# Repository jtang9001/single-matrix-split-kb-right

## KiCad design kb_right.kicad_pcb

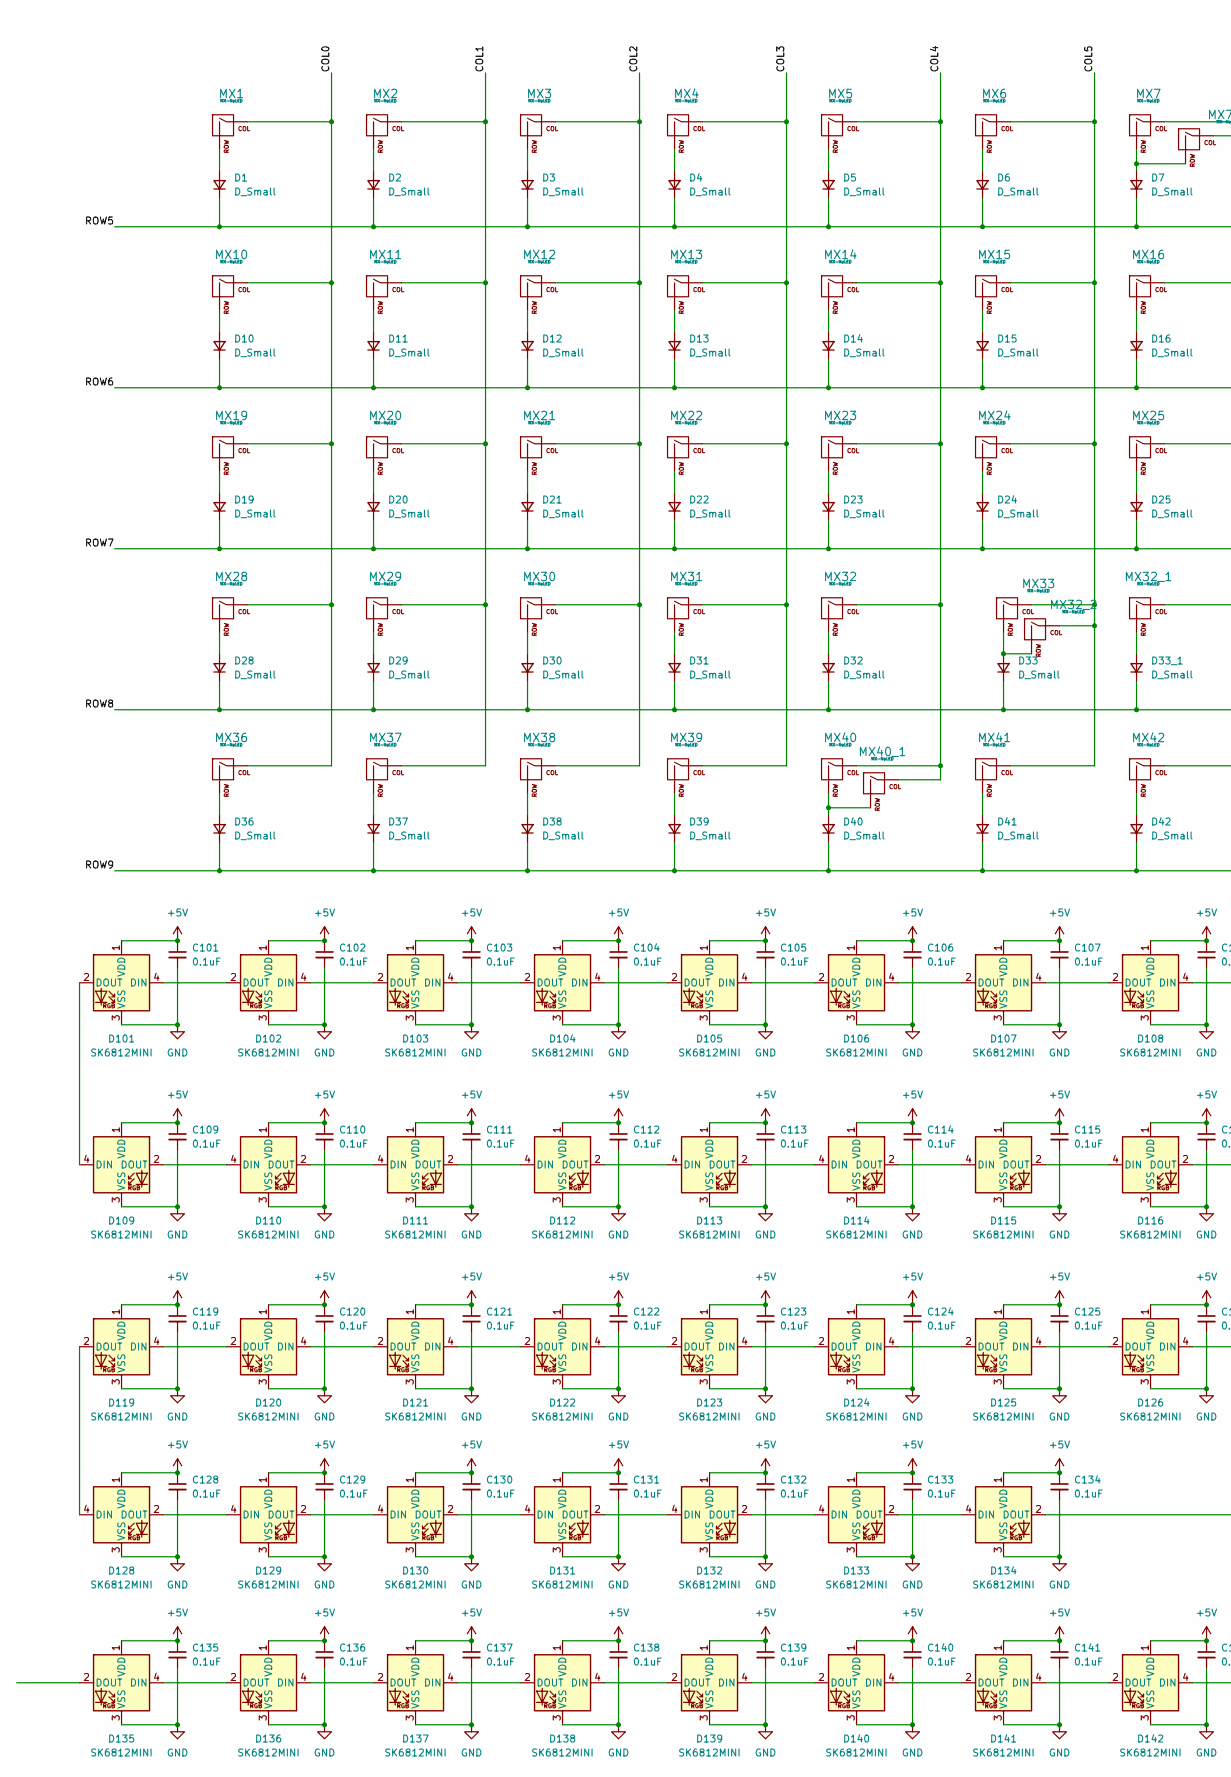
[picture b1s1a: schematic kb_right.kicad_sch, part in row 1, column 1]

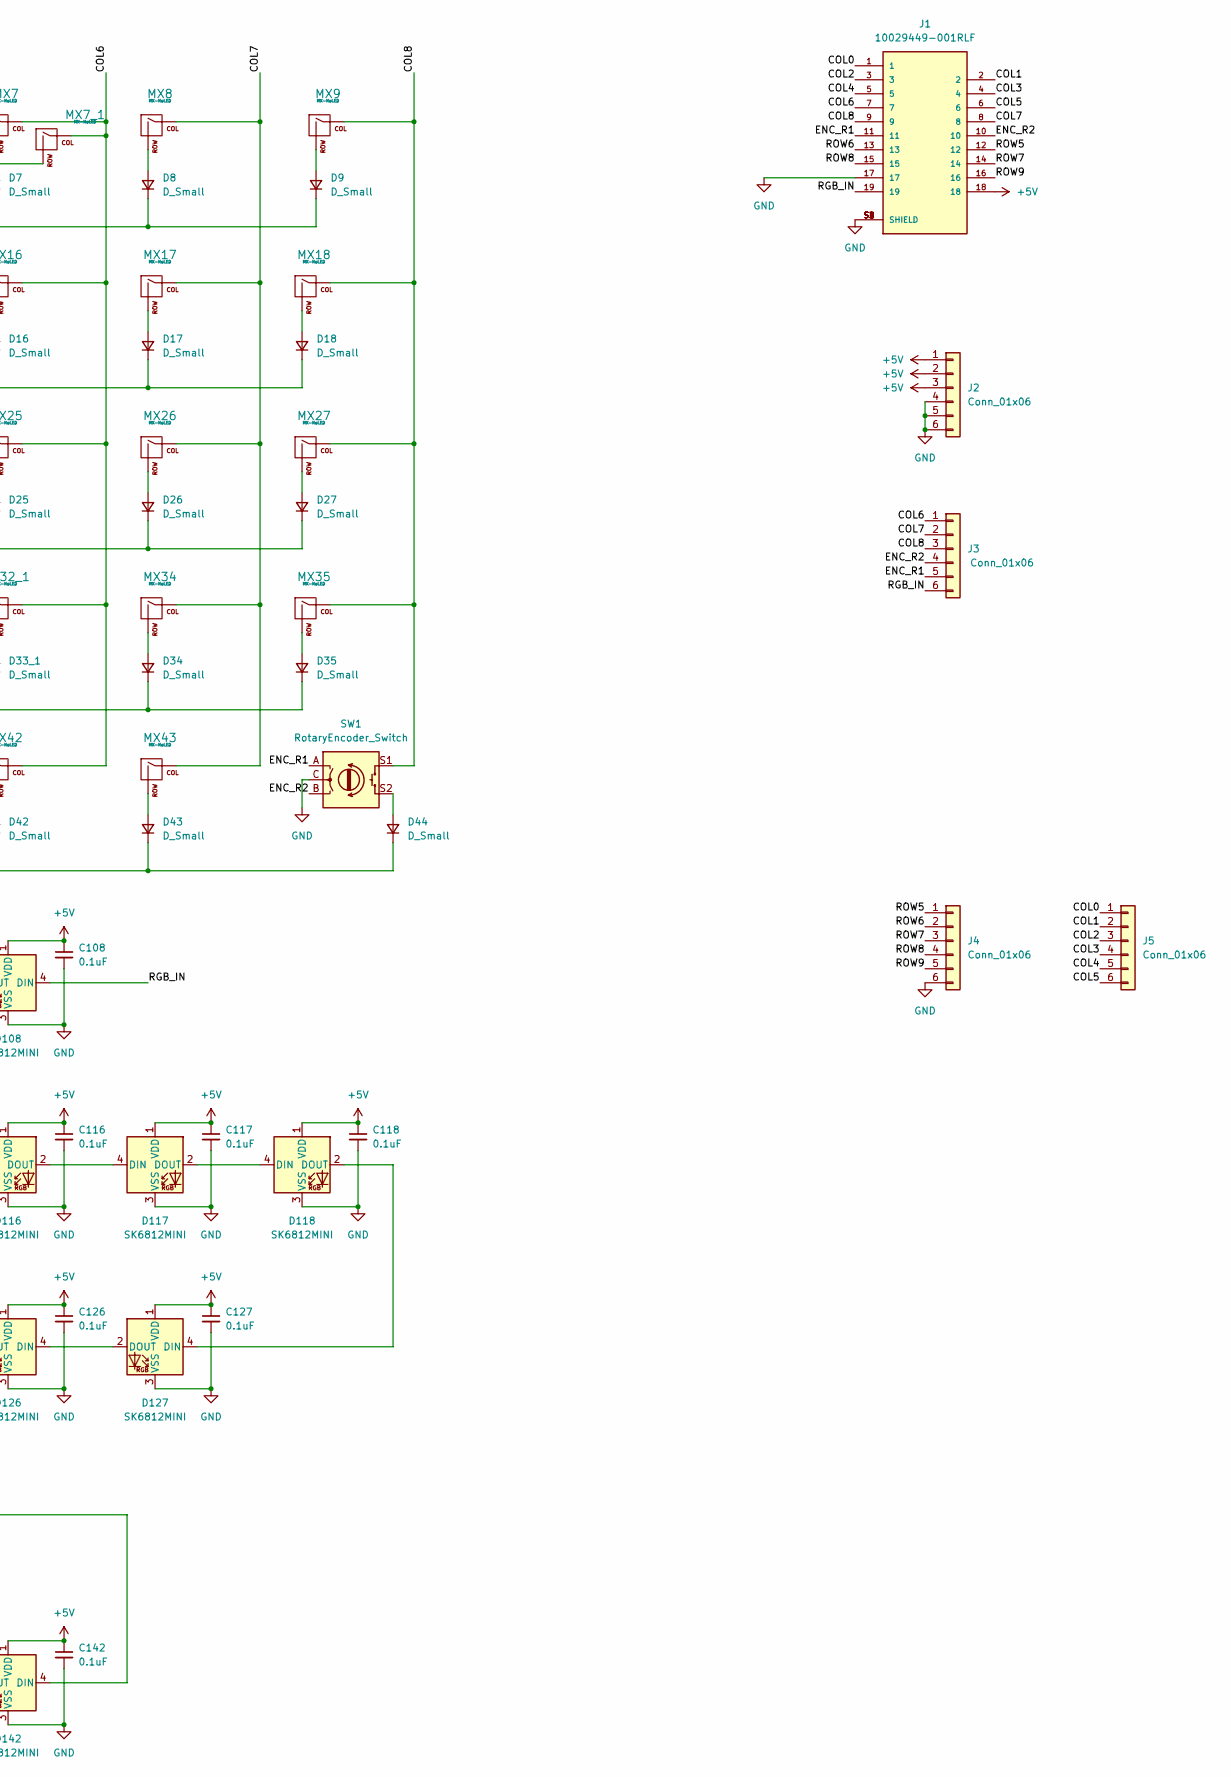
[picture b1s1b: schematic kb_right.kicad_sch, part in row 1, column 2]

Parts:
C101, C102, C103, C104, C105, C106, C107, C108, C109, C110, C111, C112, C113, C114, C115, C116, C117, C118, C119, C120, C121, C122, C123, C124, C125, C126, C127, C128, C129, C130, C131, C132, C133, C134, C135, C136, C137, C138, C139, C140, C141, C142: 0.1uF; C_0805_2012Metric_Pad1.18x1.45mm_HandSolder
D1, D2, D3, D4, D5, D6, D10, D11, D12, D13, D14, D15, D19, D20, D21, D22, D23, D24, D28, D29, D30, D31, D32, D33, D36, D37, D38, D39, D40, D41: D_Small; Diode-Hybrid-Back
D7, D8, D9, D16, D17, D18, D25, D26, D27, D33_1, D34, D35, D42, D43, D44: D_Small; D_SOD-123
D101, D102, D103, D104, D105, D106, D107, D108, D109, D110, D111, D112, D113, D114, D115, D116, D117, D118, D119, D120, D121, D122, D123, D124, D125, D126, D127, D128, D129, D130, D131, D132, D133, D134, D135, D136, D137, D138, D139, D140, D141, D142: SK6812MINI; SK6812-MINI-E
J1: 10029449-001RLF; AMPHENOL_10029449-001RLF; PARTREV V
J2, J3, J4, J5: Conn_01x06; PinHeader_1x06_P2.54mm_Vertical
MX1, MX2, MX3, MX4, MX5, MX6, MX7, MX8, MX9, MX10, MX11, MX12, MX13, MX14, MX15, MX16, MX18, MX19, MX20, MX21, MX22, MX23, MX24, MX26, MX27, MX28, MX29, MX30, MX31, MX32, MX32_1, MX34, MX35, MX41, MX42, MX43: MX-NoLED; MXOnly-1U-Hotswap
MX7_1: MX-NoLED; MXOnly-2U-Hotswap
MX17, MX36, MX40_1: MX-NoLED; MXOnly-1.5U-Hotswap
MX25: MX-NoLED; MXOnly-2.25U-Hotswap
MX32_2: MX-NoLED; MXOnly-1.75U-Hotswap
MX33: MX-NoLED; MXOnly-2.75U-Hotswap
MX37, MX38, MX39, MX40: MX-NoLED; MXOnly-1.25U-Hotswap
SW1: RotaryEncoder_Switch; RotaryEncoder_EC11

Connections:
+5V: C101.1, C102.1, C103.1, C104.1, C105.1, C106.1, C107.1, C108.1, C109.1, C110.1, C111.1, C112.1, C113.1, C114.1, C115.1, C116.1, C117.1, C118.1, C119.1, C120.1, C121.1, C122.1, C123.1, C124.1, C125.1, C126.1, C127.1, C128.1, C129.1, C130.1, C131.1, C132.1, C133.1, C134.1, C135.1, C136.1, C137.1, C138.1, C139.1, C140.1, C141.1, C142.1, D101.1 (VDD), D102.1 (VDD), D103.1 (VDD), D104.1 (VDD), D105.1 (VDD), D106.1 (VDD), D107.1 (VDD), D108.1 (VDD), D109.1 (VDD), D110.1 (VDD), D111.1 (VDD), D112.1 (VDD), D113.1 (VDD), D114.1 (VDD), D115.1 (VDD), D116.1 (VDD), D117.1 (VDD), D118.1 (VDD), D119.1 (VDD), D120.1 (VDD), D121.1 (VDD), D122.1 (VDD), D123.1 (VDD), D124.1 (VDD), D125.1 (VDD), D126.1 (VDD), D127.1 (VDD), D128.1 (VDD), D129.1 (VDD), D130.1 (VDD), D131.1 (VDD), D132.1 (VDD), D133.1 (VDD), D134.1 (VDD), D135.1 (VDD), D136.1 (VDD), D137.1 (VDD), D138.1 (VDD), D139.1 (VDD), D140.1 (VDD), D141.1 (VDD), D142.1 (VDD), J1.18, J2.1, J2.2, J2.3
/COL0: J1.1, J5.1, MX1.1 (COL), MX10.1 (COL), MX19.1 (COL), MX28.1 (COL), MX36.1 (COL)
/COL1: J1.2, J5.2, MX2.1 (COL), MX11.1 (COL), MX20.1 (COL), MX29.1 (COL), MX37.1 (COL)
/COL2: J1.3, J5.3, MX3.1 (COL), MX12.1 (COL), MX21.1 (COL), MX30.1 (COL), MX38.1 (COL)
/COL3: J1.4, J5.4, MX4.1 (COL), MX13.1 (COL), MX22.1 (COL), MX31.1 (COL), MX39.1 (COL)
/COL4: J1.5, J5.5, MX5.1 (COL), MX14.1 (COL), MX23.1 (COL), MX32.1 (COL), MX40.1 (COL), MX40_1.1 (COL)
/COL5: J1.6, J5.6, MX6.1 (COL), MX15.1 (COL), MX24.1 (COL), MX32_2.1 (COL), MX33.1 (COL), MX41.1 (COL)
/COL6: J1.7, J3.1, MX7.1 (COL), MX7_1.1 (COL), MX16.1 (COL), MX25.1 (COL), MX32_1.1 (COL), MX42.1 (COL)
/COL7: J1.8, J3.2, MX8.1 (COL), MX17.1 (COL), MX26.1 (COL), MX34.1 (COL), MX43.1 (COL)
/COL8: J1.9, J3.3, MX9.1 (COL), MX18.1 (COL), MX27.1 (COL), MX35.1 (COL), SW1.S1
/ENC_R1: J1.11, J3.5, SW1.A
/ENC_R2: J1.10, J3.4, SW1.B
/RGB_IN: D108.4 (DIN), J1.19, J3.6
/ROW5: D1.1 (K), D2.1 (K), D3.1 (K), D4.1 (K), D5.1 (K), D6.1 (K), D7.1 (K), D8.1 (K), D9.1 (K), J1.12, J4.1
/ROW6: D10.1 (K), D11.1 (K), D12.1 (K), D13.1 (K), D14.1 (K), D15.1 (K), D16.1 (K), D17.1 (K), D18.1 (K), J1.13, J4.2
/ROW7: D19.1 (K), D20.1 (K), D21.1 (K), D22.1 (K), D23.1 (K), D24.1 (K), D25.1 (K), D26.1 (K), D27.1 (K), J1.14, J4.3
/ROW8: D28.1 (K), D29.1 (K), D30.1 (K), D31.1 (K), D32.1 (K), D33.1 (K), D33_1.1 (K), D34.1 (K), D35.1 (K), J1.15, J4.4
/ROW9: D36.1 (K), D37.1 (K), D38.1 (K), D39.1 (K), D40.1 (K), D41.1 (K), D42.1 (K), D43.1 (K), D44.1 (K), J1.16, J4.5
GND: C101.2, C102.2, C103.2, C104.2, C105.2, C106.2, C107.2, C108.2, C109.2, C110.2, C111.2, C112.2, C113.2, C114.2, C115.2, C116.2, C117.2, C118.2, C119.2, C120.2, C121.2, C122.2, C123.2, C124.2, C125.2, C126.2, C127.2, C128.2, C129.2, C130.2, C131.2, C132.2, C133.2, C134.2, C135.2, C136.2, C137.2, C138.2, C139.2, C140.2, C141.2, C142.2, D101.3 (VSS), D102.3 (VSS), D103.3 (VSS), D104.3 (VSS), D105.3 (VSS), D106.3 (VSS), D107.3 (VSS), D108.3 (VSS), D109.3 (VSS), D110.3 (VSS), D111.3 (VSS), D112.3 (VSS), D113.3 (VSS), D114.3 (VSS), D115.3 (VSS), D116.3 (VSS), D117.3 (VSS), D118.3 (VSS), D119.3 (VSS), D120.3 (VSS), D121.3 (VSS), D122.3 (VSS), D123.3 (VSS), D124.3 (VSS), D125.3 (VSS), D126.3 (VSS), D127.3 (VSS), D128.3 (VSS), D129.3 (VSS), D130.3 (VSS), D131.3 (VSS), D132.3 (VSS), D133.3 (VSS), D134.3 (VSS), D135.3 (VSS), D136.3 (VSS), D137.3 (VSS), D138.3 (VSS), D139.3 (VSS), D140.3 (VSS), D141.3 (VSS), D142.3 (VSS), J1.17, J1.S1 (SHIELD), J1.S2 (SHIELD), J1.S3 (SHIELD), J1.S4 (SHIELD), J2.4, J2.5, J2.6, J4.6, SW1.C
unnamed: D1.2 (A), MX1.2 (ROW)
unnamed: D2.2 (A), MX2.2 (ROW)
unnamed: D3.2 (A), MX3.2 (ROW)
unnamed: D4.2 (A), MX4.2 (ROW)
unnamed: D5.2 (A), MX5.2 (ROW)
unnamed: D6.2 (A), MX6.2 (ROW)
unnamed: D7.2 (A), MX7.2 (ROW), MX7_1.2 (ROW)
unnamed: D8.2 (A), MX8.2 (ROW)
unnamed: D9.2 (A), MX9.2 (ROW)
unnamed: D10.2 (A), MX10.2 (ROW)
unnamed: D11.2 (A), MX11.2 (ROW)
unnamed: D12.2 (A), MX12.2 (ROW)
unnamed: D13.2 (A), MX13.2 (ROW)
unnamed: D14.2 (A), MX14.2 (ROW)
unnamed: D15.2 (A), MX15.2 (ROW)
unnamed: D16.2 (A), MX16.2 (ROW)
unnamed: D17.2 (A), MX17.2 (ROW)
unnamed: D18.2 (A), MX18.2 (ROW)
unnamed: D19.2 (A), MX19.2 (ROW)
unnamed: D20.2 (A), MX20.2 (ROW)
unnamed: D21.2 (A), MX21.2 (ROW)
unnamed: D22.2 (A), MX22.2 (ROW)
unnamed: D23.2 (A), MX23.2 (ROW)
unnamed: D24.2 (A), MX24.2 (ROW)
unnamed: D25.2 (A), MX25.2 (ROW)
unnamed: D26.2 (A), MX26.2 (ROW)
unnamed: D27.2 (A), MX27.2 (ROW)
unnamed: D28.2 (A), MX28.2 (ROW)
unnamed: D29.2 (A), MX29.2 (ROW)
unnamed: D30.2 (A), MX30.2 (ROW)
unnamed: D31.2 (A), MX31.2 (ROW)
unnamed: D32.2 (A), MX32.2 (ROW)
unnamed: D33.2 (A), MX32_2.2 (ROW), MX33.2 (ROW)
unnamed: D33_1.2 (A), MX32_1.2 (ROW)
unnamed: D34.2 (A), MX34.2 (ROW)
unnamed: D35.2 (A), MX35.2 (ROW)
unnamed: D36.2 (A), MX36.2 (ROW)
unnamed: D37.2 (A), MX37.2 (ROW)
unnamed: D38.2 (A), MX38.2 (ROW)
unnamed: D39.2 (A), MX39.2 (ROW)
unnamed: D40.2 (A), MX40.2 (ROW), MX40_1.2 (ROW)
unnamed: D41.2 (A), MX41.2 (ROW)
unnamed: D42.2 (A), MX42.2 (ROW)
unnamed: D43.2 (A), MX43.2 (ROW)
unnamed: D44.2 (A), SW1.S2
unnamed: D101.2 (DOUT), D109.4 (DIN)
unnamed: D101.4 (DIN), D102.2 (DOUT)
unnamed: D102.4 (DIN), D103.2 (DOUT)
unnamed: D103.4 (DIN), D104.2 (DOUT)
unnamed: D104.4 (DIN), D105.2 (DOUT)
unnamed: D105.4 (DIN), D106.2 (DOUT)
unnamed: D106.4 (DIN), D107.2 (DOUT)
unnamed: D107.4 (DIN), D108.2 (DOUT)
unnamed: D109.2 (DOUT), D110.4 (DIN)
unnamed: D110.2 (DOUT), D111.4 (DIN)
unnamed: D111.2 (DOUT), D112.4 (DIN)
unnamed: D112.2 (DOUT), D113.4 (DIN)
unnamed: D113.2 (DOUT), D114.4 (DIN)
unnamed: D114.2 (DOUT), D115.4 (DIN)
unnamed: D115.2 (DOUT), D116.4 (DIN)
unnamed: D116.2 (DOUT), D117.4 (DIN)
unnamed: D117.2 (DOUT), D118.4 (DIN)
unnamed: D118.2 (DOUT), D127.4 (DIN)
unnamed: D119.2 (DOUT), D128.4 (DIN)
unnamed: D119.4 (DIN), D120.2 (DOUT)
unnamed: D120.4 (DIN), D121.2 (DOUT)
unnamed: D121.4 (DIN), D122.2 (DOUT)
unnamed: D122.4 (DIN), D123.2 (DOUT)
unnamed: D123.4 (DIN), D124.2 (DOUT)
unnamed: D124.4 (DIN), D125.2 (DOUT)
unnamed: D125.4 (DIN), D126.2 (DOUT)
unnamed: D126.4 (DIN), D127.2 (DOUT)
unnamed: D128.2 (DOUT), D129.4 (DIN)
unnamed: D129.2 (DOUT), D130.4 (DIN)
unnamed: D130.2 (DOUT), D131.4 (DIN)
unnamed: D131.2 (DOUT), D132.4 (DIN)
unnamed: D132.2 (DOUT), D133.4 (DIN)
unnamed: D133.2 (DOUT), D134.4 (DIN)
unnamed: D134.2 (DOUT), D142.4 (DIN)
unnamed: D135.4 (DIN), D136.2 (DOUT)
unnamed: D136.4 (DIN), D137.2 (DOUT)
unnamed: D137.4 (DIN), D138.2 (DOUT)
unnamed: D138.4 (DIN), D139.2 (DOUT)
unnamed: D139.4 (DIN), D140.2 (DOUT)
unnamed: D140.4 (DIN), D141.2 (DOUT)
unnamed: D141.4 (DIN), D142.2 (DOUT)

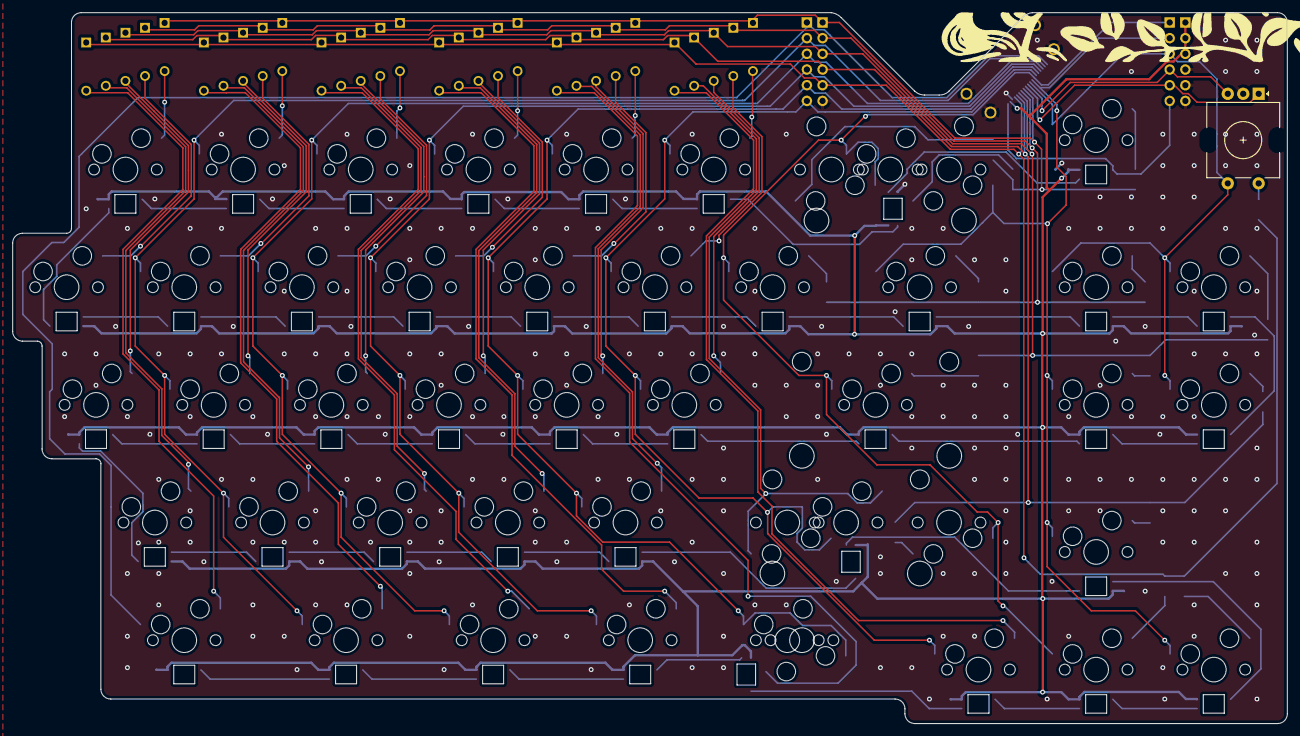
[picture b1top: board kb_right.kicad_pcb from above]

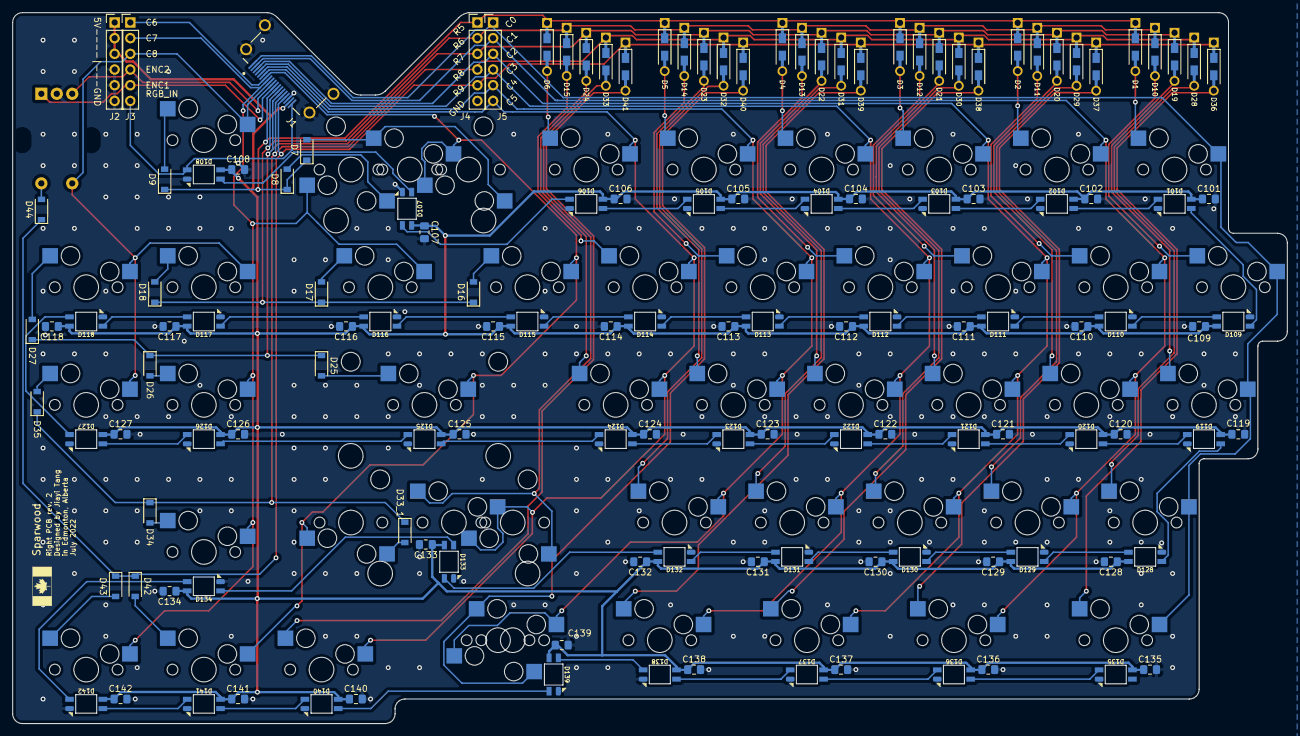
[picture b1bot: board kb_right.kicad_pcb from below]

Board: 2 copper layers, 206.4 x 115.1 mm, 182 parts (104 on the bottom side), 105 nets.

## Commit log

2022-07-10 added libraries, started project
2022-07-10 now added library
2022-07-10 matrix sch done
2022-07-10 added footprints
2022-07-10 laid out right keys
2022-07-10 added smd caps
2022-07-10 routed matrix
2022-07-10 labelled hdmi port
2022-07-10 most routing done
2022-07-10 tearing up tracks to fix sk6812
2022-07-10 fixed sk6812 routing
2022-07-11 add 3d model
2022-07-11 did and undid top edge
2022-07-11 added 3d model
2022-07-14 add test points
2022-07-14 add silkscreen
2022-07-14 small change
2022-07-14 shift hdmi cutout
2022-07-14 changed sk6812 footprints
2022-07-14 change sk6812 pads again to 0.3mm
2022-07-14 change cap values
2022-07-16 added 1.75u right shift
2022-07-16 revise right shfit route
2022-07-16 fixed split right shift
2022-07-19 last commit before switching to through hole
2022-07-19 start thru hole
2022-07-19 try again - add rgb routing
2022-07-20 routed test points
2022-07-20 added ground vias
2022-07-20 add via stitching
2022-07-21 add pcb art
2022-07-22 add silkscreen art lol
2022-07-26 change flag?
2022-07-26 flag checked
2022-07-27 add sideways encoder
2022-07-28 clipped art edges
2022-07-28 added rgb end pinout
2022-07-28 update step file
2022-07-28 changed pinout footprint
2022-07-29 before double-check
2022-07-29 before sending to jlc
2022-07-29 cad checked
2022-07-30 version sent to jlc
2022-07-30 eod jul 29
